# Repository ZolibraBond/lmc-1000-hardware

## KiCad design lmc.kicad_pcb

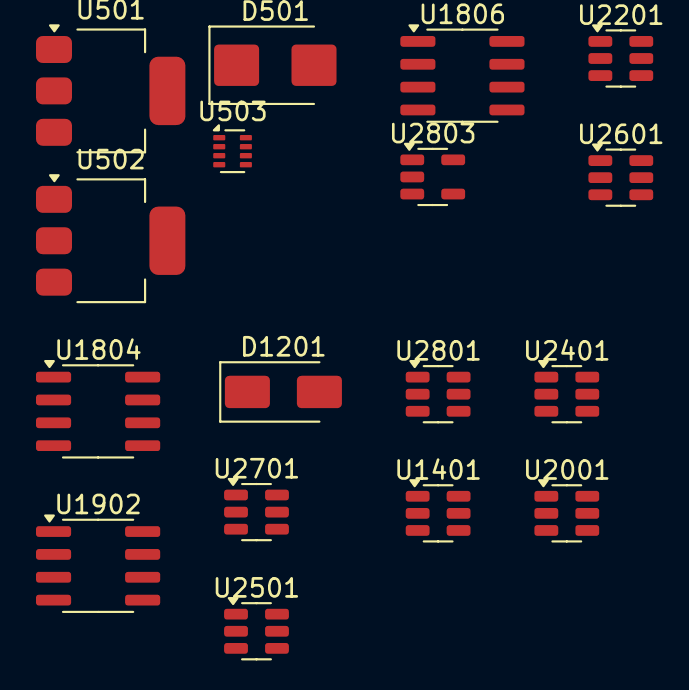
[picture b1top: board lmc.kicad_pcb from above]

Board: 2 copper layers, 17 parts (0 on the bottom side), 11 nets, no tracks yet.

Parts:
D501: SM6T30A; D_SMB
D1201: SMAJ5.0A; D_SMA
U501: AMS1117-3.3; SOT-223-3_TabPin2
U502: AMS1117-5.0; SOT-223-3_TabPin2
U503: TPS6293X; SOT-583-8
U1401, U2001, U2201, U2401, U2501, U2601, U2701, U2801: BD_2EDN8533FXTMA1; SOT-23-6
U1804, U1806, U1902: ACS712xLCTR-30A; SOIC-8_3.9x4.9mm_P1.27mm
U2803: MCP6001-OT; SOT-23-5

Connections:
+3V3: U1804.8 (VCC), U1806.8 (VCC), U1902.8 (VCC), U2803.5 (V+)
+9V: U1401.6 (VDD), U2001.6 (VDD), U2201.6 (VDD), U2401.6 (VDD), U2501.6 (VDD), U2601.6 (VDD), U2701.6 (VDD), U2801.6 (VDD)
+24V: D501.1 (A1), U503.3 (VIN)
/Project Architecture/PWM Channels/LED Current Sense/LED_CURRENT: U1806.7 (VIOUT), U2803.4 (-)
/Project Architecture/PWM Channels/LED Current Sense/LED_POWER_INPUT: U1806.1 (IP+), U1806.2 (IP+)
/Project Architecture/PWM Channels/LED Current Sense/LED_POWER_OUTPUT: U1806.3 (IP-), U1806.4 (IP-)
GND: D501.2 (A2), D1201.2 (A2), U501.1 (GND), U502.1 (GND), U503.4 (GND), U1401.3 (GND), U1804.5 (GND), U1806.5 (GND), U1902.5 (GND), U2001.3 (GND), U2201.3 (GND), U2401.3 (GND), U2501.3 (GND), U2601.3 (GND), U2701.3 (GND), U2801.3 (GND), U2803.2 (V-)
unnamed: U1804.1 (IP+), U1804.2 (IP+)
unnamed: U1902.1 (IP+), U1902.2 (IP+)
unnamed: U1804.3 (IP-), U1804.4 (IP-)
unnamed: U1902.3 (IP-), U1902.4 (IP-)

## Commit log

2025-12-09 init
2025-12-09 git: add gitignore
2025-12-09 schematic: continue project architecture
2025-12-10 schematic: add project structure wiring
2025-12-17 Add power stages
2025-12-19 Add power supplies
2025-12-19 Remove STM
